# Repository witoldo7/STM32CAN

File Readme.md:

# STM32CAN - WQCAN
The idea of the project is to provide CAN and BDM functionality for Saab Trionic 8 ECU. 

## Currently supported:
* CombiBeckend - For CAN operation work fine.
* SocketCAN - Most of the driver impl is done.
     - can0: CAN2.0/FDCAN - various speed can be defined, loop back, one shoot, listen only, FD mode, FD_NON_ISO, TDC_AUTO
     - can1: SWCAN - 33.3k and 83.3k, loop back, one shoot, listen only.
     - TODO: BERR_REPORTING
* SAE J2534 - Support for Windows and Linux.
     - ISO14230: Tested with Tech2Win and Saab 9-5 DICE,
     - ISO15765: Tested with GenericDiagnosticTool, OpenVehicleDiag and Trionic8 ECU, SW_ISO15765_PS on pin1,
     - CAN: Tested with TrionicCanFlasher, Txloger. Read T8 ECU flash time: 38s ;)

## TODO
* BDM - Needs rework.

## License
Apache2

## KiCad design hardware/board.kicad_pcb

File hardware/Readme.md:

# WQCAN Hardware

Folder contain costom dev board for MCUDev DevEBox STM32H7XX_M.

## License
[MIT](https://choosealicense.com/licenses/mit/)

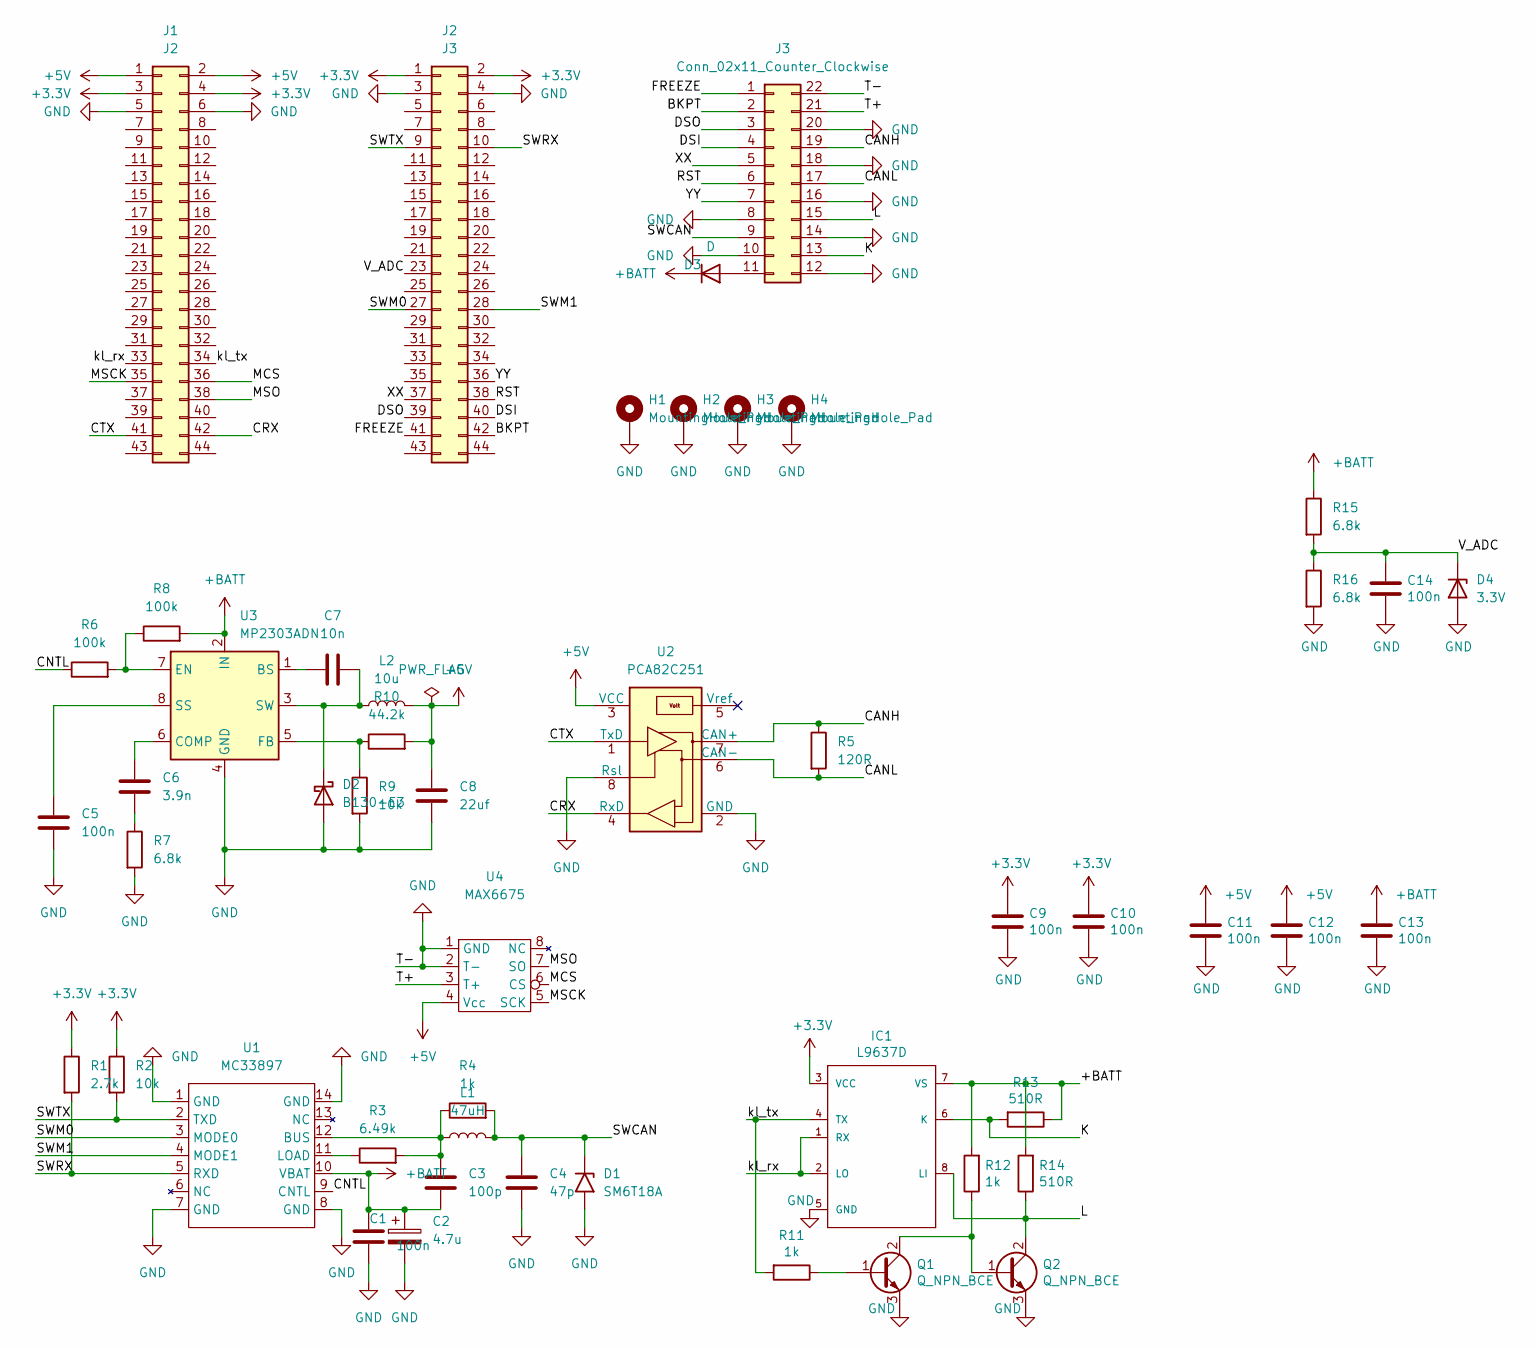
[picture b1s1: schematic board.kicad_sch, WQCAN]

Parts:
C1: 100n; D_1206_3216Metric_Pad1.42x1.75mm_HandSolder
C2: 4.7u; CP_Elec_4x4.5
C3: 100p; C_1206_3216Metric_Pad1.33x1.80mm_HandSolder
C4: 47p; C_1206_3216Metric_Pad1.33x1.80mm_HandSolder
C5: 100n; C_1206_3216Metric_Pad1.33x1.80mm_HandSolder
C6: 3.9n; C_1206_3216Metric_Pad1.33x1.80mm_HandSolder
C7: 10n; C_1206_3216Metric_Pad1.33x1.80mm_HandSolder
C8: 22uf; C_2220_5650Metric_Pad1.97x5.40mm_HandSolder
C9, C10, C11, C12, C13, C14: 100n; C_1206_3216Metric_Pad1.33x1.80mm_HandSolder; LCSC C52923
D1: SM6T18A; D_SMB
D2: B130-E3; D_SMA
D3: D; D_1210_3225Metric_Pad1.42x2.65mm_HandSolder
D4: 3.3V; D_1206_3216Metric_Pad1.42x1.75mm_HandSolder
H1, H2, H3, H4: MountingHole_Pad; MountingHole_3.2mm_M3
IC1: L9637D; SO-8_5.3x6.2mm_P1.27mm
J1: J2; PinHeader_2x22_P2.54mm_Vertical
J2: J3; PinHeader_2x22_P2.54mm_Vertical
J3: Conn_02x11_Counter_Clockwise; PinHeader_2x11_P2.54mm_Horizontal
L1: 47uH; L_1210_3225Metric_Pad1.42x2.65mm_HandSolder
L2: 10u; L_7.3x7.3_H3.5
Q1, Q2: Q_NPN_BCE; SOT-23_Handsoldering
R1: 2.7k; R_1206_3216Metric_Pad1.30x1.75mm_HandSolder
R2, R9: 10k; R_1206_3216Metric_Pad1.30x1.75mm_HandSolder
R3: 6.49k; R_1206_3216Metric_Pad1.30x1.75mm_HandSolder
R4, R11, R12: 1k; R_1206_3216Metric_Pad1.30x1.75mm_HandSolder
R5: 120R; R_1206_3216Metric_Pad1.30x1.75mm_HandSolder
R6, R8: 100k; R_1206_3216Metric_Pad1.30x1.75mm_HandSolder
R7, R15, R16: 6.8k; R_1206_3216Metric_Pad1.30x1.75mm_HandSolder
R10: 44.2k; R_1206_3216Metric_Pad1.30x1.75mm_HandSolder
R13, R14: 510R; R_1206_3216Metric_Pad1.30x1.75mm_HandSolder
U1: MC33897; SO-14_3.9x8.65mm_P1.27mm
U2: PCA82C251; SO-8_3.9x4.9mm_P1.27mm
U3: MP2303ADN; SOIC-8-1EP_3.9x4.9mm_P1.27mm_EP2.62x3.51mm
U4: MAX6675; SO-8_5.3x6.2mm_P1.27mm

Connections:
+3V3: C9.1, C10.1, IC1.3 (VCC), J1.3, J1.4, J2.1, J2.2, R1.1, R2.1
+5V: C8.1, C11.1, C12.1, J1.1, J1.2, L2.2, R10.2, U2.3 (VCC), U4.4 (Vcc)
+BATT: C1.1, C2.1, C3.2, C13.1, D3.1 (K), IC1.7 (VS), R8.2, R12.2, R13.1, R14.2, R15.1, U1.10 (VBAT), U3.2 (IN)
/BKPT: J2.42, J3.2
/CANH: J3.19, R5.1, U2.7 (CAN+)
/CANL: J3.17, R5.2, U2.6 (CAN-)
/CNTL: R6.1, U1.9 (CNTL)
/CRX: J1.42, U2.4 (RxD)
/CTX: J1.41, U2.1 (TxD)
/DSI: J2.40, J3.4
/DSO: J2.39, J3.3
/FREEZE: J2.41, J3.1
/K: IC1.6 (K), J3.13, R13.2
/L: IC1.8 (LI), J3.15, Q2.2 (C), R14.1
/MCS: J1.36, U4.6 (CS)
/MSCK: J1.35, U4.5 (SCK)
/MSO: J1.38, U4.7 (SO)
/RST: J2.38, J3.6
/SWCAN: C4.1, D1.1 (A1), J3.9, L1.2, R4.2
/SWM0: J2.27, U1.3 (MODE0)
/SWM1: J2.28, U1.4 (MODE1)
/SWRX: J2.10, R1.2, U1.5 (RXD)
/SWTX: J2.9, R2.2, U1.2 (TXD)
/T+: J3.21, U4.3 (T+)
/V_ADC: C14.1, D4.1 (K), J2.23, R15.2, R16.1
/XX: J2.37, J3.5
/YY: J2.36, J3.7
/kl_rx: IC1.1 (RX), IC1.2 (LO), J1.33
/kl_tx: IC1.4 (TX), J1.34, R11.2
GND: C1.2, C2.2, C4.2, C5.2, C8.2, C9.2, C10.2, C11.2, C12.2, C13.2, C14.2, D1.2 (A2), D2.2 (A), D4.2 (A), H1.1, H2.1, H3.1, H4.1, IC1.5 (GND), J1.5, J1.6, J2.3, J2.4, J3.8, J3.10, J3.12, J3.14, J3.16, J3.18, J3.20, J3.22, Q1.3 (E), Q2.3 (E), R7.2, R9.2, R16.2, U1.1 (GND), U1.7 (GND), U1.8 (GND), U1.14 (GND), U2.2 (GND), U2.8 (Rsl), U3.4 (GND), U4.1 (GND), U4.2 (T-)
unnamed: C3.1, L1.1, R3.2, R4.1, U1.12 (BUS)
unnamed: C5.1, U3.8 (SS)
unnamed: C6.1, U3.6 (COMP)
unnamed: C6.2, R7.1
unnamed: C7.1, U3.1 (BS)
unnamed: C7.2, D2.1 (K), L2.1, U3.3 (SW)
unnamed: D3.2 (A), J3.11
unnamed: Q1.1 (B), R11.1
unnamed: Q1.2 (C), Q2.1 (B), R12.1
unnamed: R3.1, U1.11 (LOAD)
unnamed: R6.2, R8.1, U3.7 (EN)
unnamed: R9.1, R10.1, U3.5 (FB)

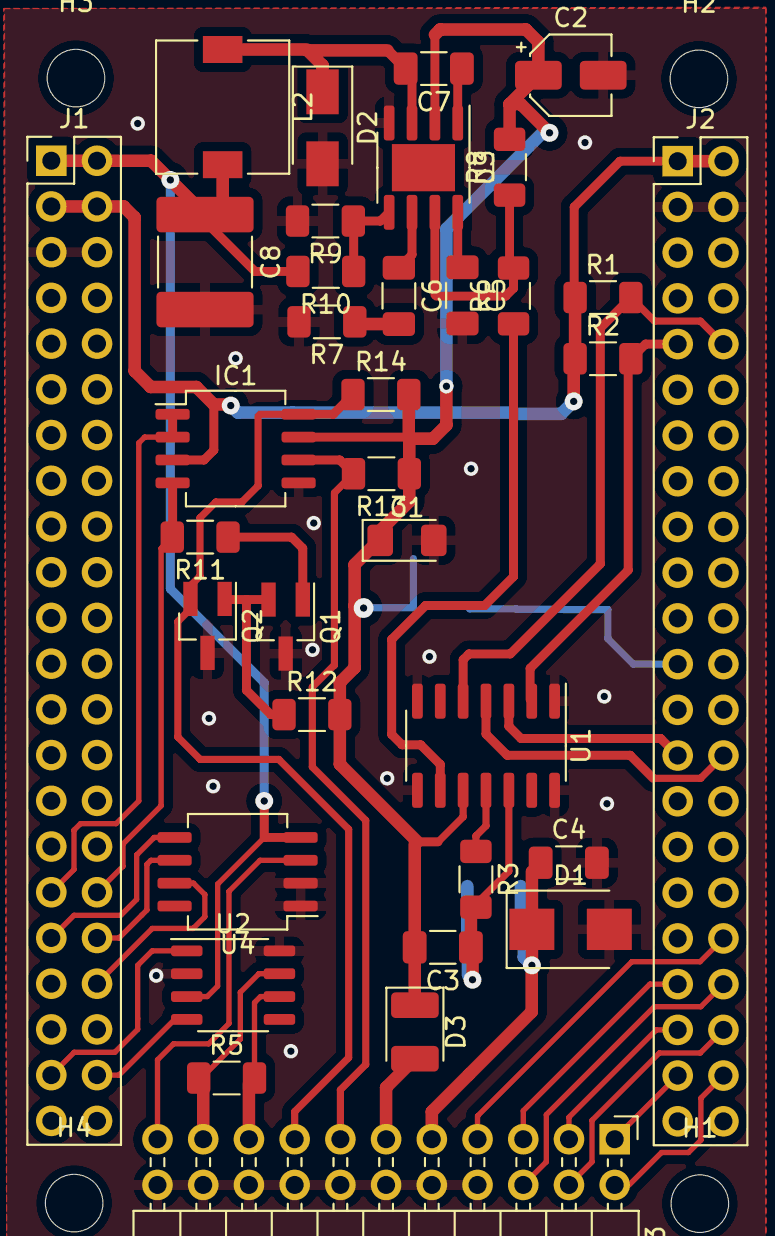
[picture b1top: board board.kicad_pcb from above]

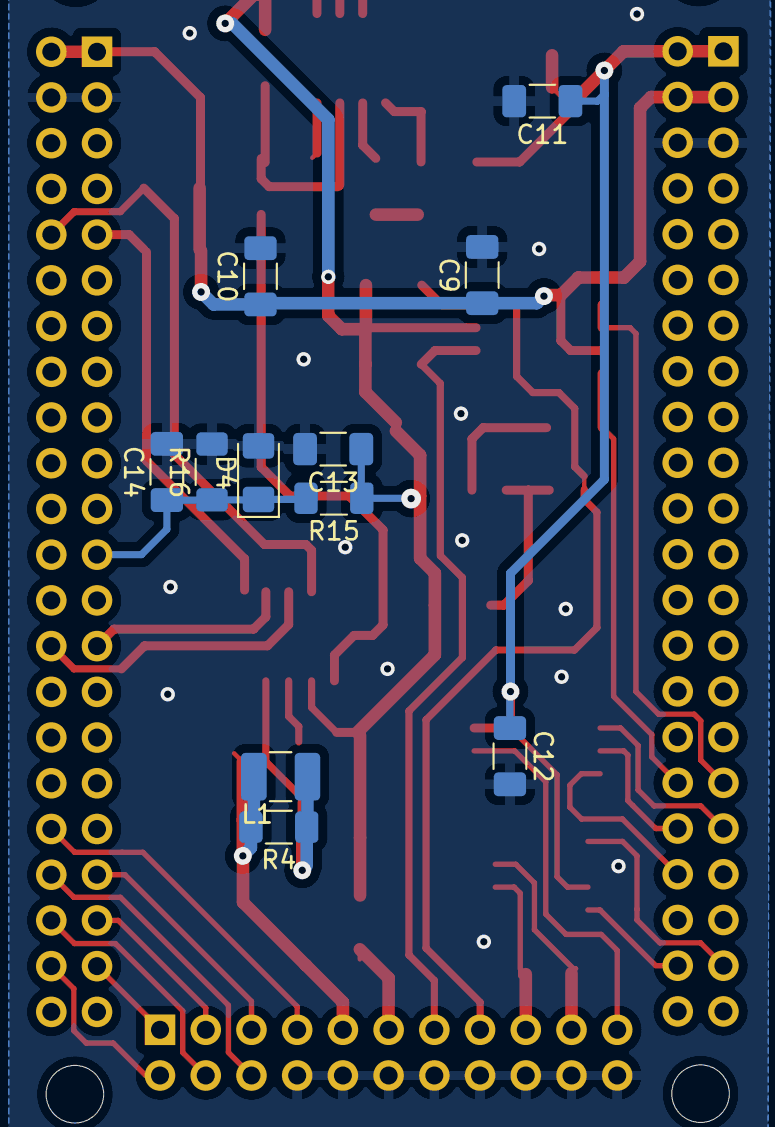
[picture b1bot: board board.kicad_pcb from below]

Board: 2 copper layers, 50 parts (11 on the bottom side), 42 nets.

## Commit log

2022-02-13 add initial USB-CAN support for combi backend
    -on top of ChibiOS/RT stable_21.6.x
    -eclipse project
2022-02-13 fix invalid CAN frame length
2022-02-13 code style fix
2022-02-13 ignore build files in git operations
2022-02-13 can init and filters cmd
2022-02-15 move usb function from main
2022-02-16 bdm: fix packet receiving
2022-02-17 bdm: add initial support based on just4trionic
2022-02-17 stm32f7 port
2022-02-18 can: swcan definition and configuration
2022-02-27 can: clean and remove unused
2022-02-27 drv: windows drivers
2022-03-06 drv: move windows driver
2022-03-07 can: rename constants
2022-03-07 drv: initial linux socketcan driver
2022-07-16 test maf
2022-07-17 brd: STM32H750VBT6 port
    CAN: basic standard can working, fdcan not yet, missing acceptance filters;
    USB communication: working;
2022-07-18 brd: setup gpio for existing peripherals
2022-07-18 can: ram configuration and frames filtering
2022-07-25 brd: update pinout for can board
2022-07-25 drv: fix socketcan tx/rx, add fdcan support
2022-07-25 can: add fdcan linux drv support
2022-08-04 misc: rearange structure
2022-08-05 drv: add stub j2534 driver def
2022-08-05 hw: add sample test board for DevEBox STM32H7XX_M
2022-08-21 misc: rename folders, update: readme, headers
2022-08-22 [FW][ADC] add VBAT reading
2022-08-24 [drv] fix socket can build error
2022-09-05 j2534: vbat
2022-10-03 fw: update swcan to fit socketcan drv
2022-10-03 drv: add swcan interface
2022-10-03 misc: update readme
2022-10-04 drv: packet counting by ack, define constants, clean up
2022-10-07 drv: add readme for socetcan
2022-10-07 fw: setup swcan phy mode
2022-10-08 docs: add documents
2022-10-08 drv: ignore usb interrupt interface
    interface 0 keept for comatibility with combiadapter
2023-02-13 drv: usb interface 1 provide can, ignore other
2023-02-13 drv: socketcan, fix droped packages, add ethtool interface
2023-02-13 fw: update board init
2023-02-19 fw: add usb cdc
2023-02-23 drv: initial buggy j2534 poc
2023-02-23 fw: initial buggy j2534 poc
2023-02-23 drv: socketcan filter
2023-03-03 test
2023-03-19 drv: update j2534
2023-03-19 fw: update j2534
2023-03-27 drv: j2534 update
2023-03-27 fw: j2534 update
2023-04-02 misc: update licemse, readme
2023-04-02 fw: refactor
2023-04-02 drv: refactor
2023-04-10 drv: j2534 handle ioctl, swcan, etc.
2023-04-10 misc: update gitihnore
2023-04-10 fw: j2534 add more ioctls, refactor
2023-04-10 use common header, add readme for j2534, update install
2023-04-10 drv: j2534 translate errors
2023-04-10 fw: add stub ioctls, fix swcan reading
2023-04-15 fw: kl lines setup
2023-04-15 refactor
2023-04-23 fw: iso14230 fast init, default cfg values
2023-04-23 drv: iso14230 fast init
2025-12-29 update kline fast init
2025-12-29 fw: refactor on top of ChibiOS 81fad2afecfa372f4b4e56026ad48d40d9448071
2025-12-29 drv: fix build on linux 6.18.2
2025-12-29 drv: fixe libusb reopen and debug print msg
2026-01-05 drv: update header and kline impl
2026-01-05 fw: update can, init impl of iso14230
2026-01-07 fw: kline timing update, tester present, session termination, message recv timestamp.
2026-01-07 drv: j2534 iso14230 message timestamp
2026-01-09 fw: rework CAN, add basic iso-tp support
2026-01-09 drv: add basic iso tp support
2026-01-09 fw: move default impl to separate file
2026-01-13 drv,sockecan: add hw filtering support for hscan via /sys
2026-01-13 drv,j2534: isotp write stuff
2026-01-13 fw: support for hw filters
2026-01-13 fw, use mailboxes to not block can threads, isotp stuff
2026-01-14 socketcan: swcan hw filtering via /sys, introduced cmd to clear filters
2026-01-15 reduce socketcan frames size, correct reporting tx/rx bytes fix swcan rx frames
